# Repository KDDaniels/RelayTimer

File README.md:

# Relay Timer

Simple timer with a two button interface and LCD screen to show the time remaining. Intended to control a relay but could be used for anything else really.

# Dependencies

I couldn't find it on the PlatformIO library explorer, but this project requires the **[LiquidCrystal_attiny](https://github.com/platisd/ATtiny85-LCD-library/tree/master)** library.

## Features:
- Adjustable time, goes up to 9:59:59 max by default but can be adjusted
- Timer is pausable whenever needed
- Can easily reset the timer while paused or before starting

## Wiring

Intended for an **ATtiny85**, this could definitely be ported to other microcontrollers if needed. Will need slight adjustment due to the direct port register manipulation though.

- NC = No connection
- FB = Function button
- TB = Toggle button
- SCL goes to SCL
- SDA goes to SDA
- Relay goes to a transistor (or straight to a relay if you're feeling bold (don't do that))

```
             ATtiny85
             __   __
 NC <- PB5 =|1 *-* 8|= VCC <- +5v
 FB <- PB3 =|2     7|= PB2 -> SCL
 TB <- PB4 =|3     6|= PB1 -> Relay
GND <- GND =|4_____5|= PB0 -> SDA

```

# Hardware
- ATtiny85 or another microcontroller (will require modification)
- LCD with I<sup>2</sup>C support (I'm using a 1602 screen with a PCF8574 board)
- A relay module
- Two buttons
- A single NPN transistor (I'm using a 2N2222)
- A few resistors (2 4.7kOhm and 5 1kOhm)

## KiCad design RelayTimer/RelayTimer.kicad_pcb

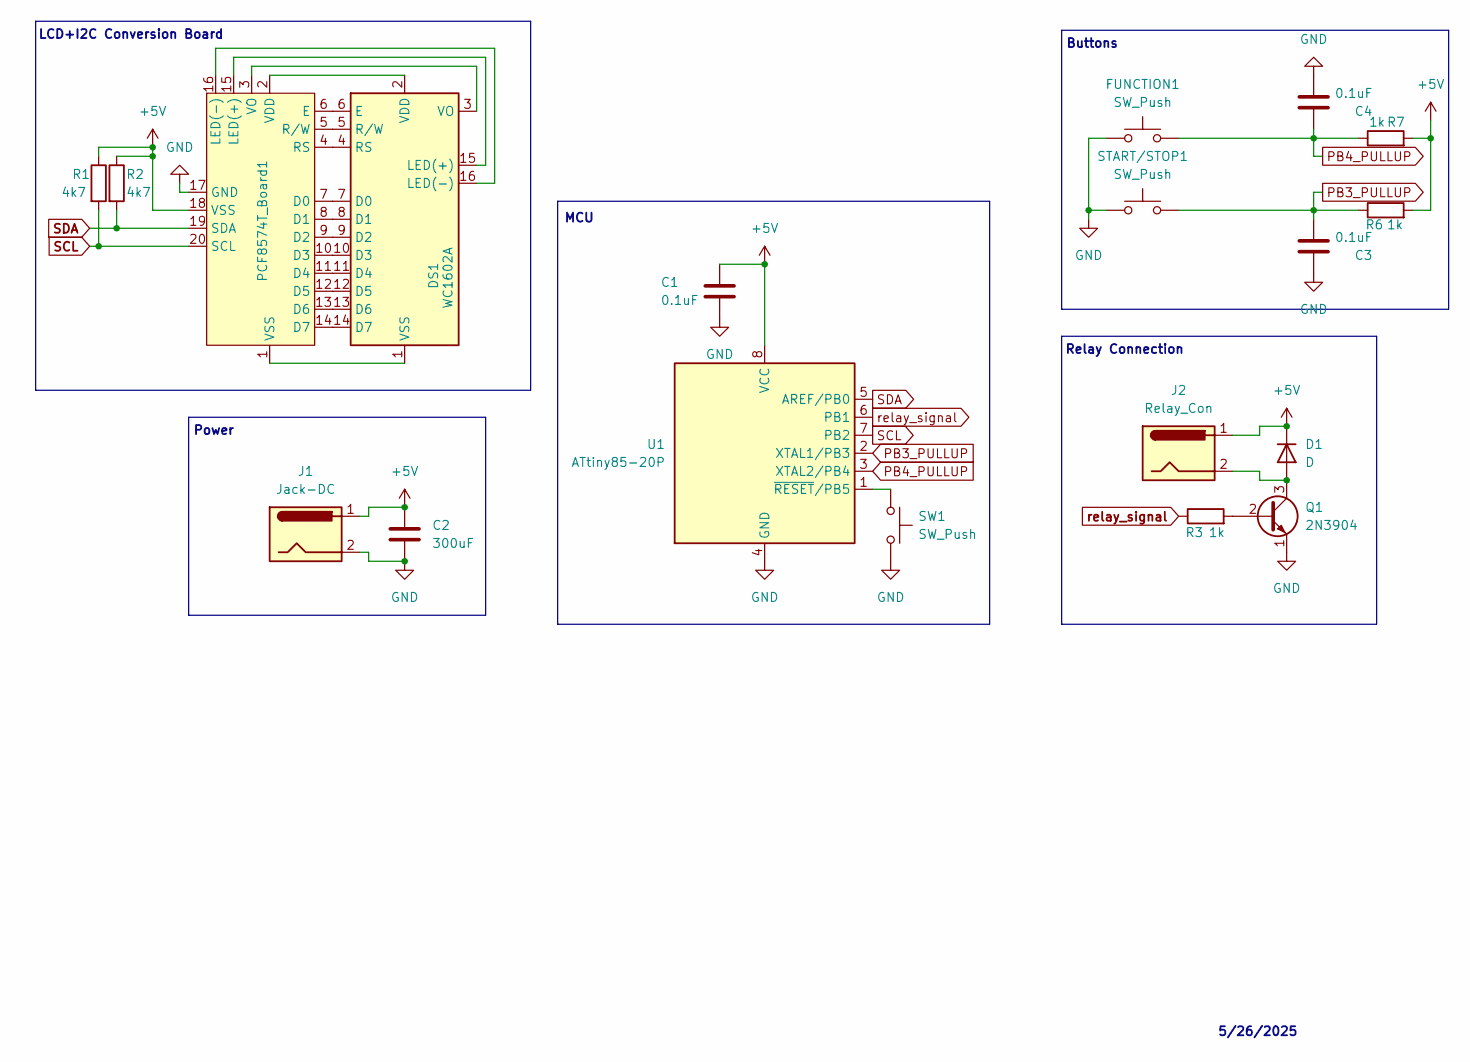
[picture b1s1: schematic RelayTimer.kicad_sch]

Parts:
C1, C3, C4: 0.1uF; C_Disc_D3.0mm_W1.6mm_P2.50mm
C2: 300uF; C_Radial_D10.0mm_H12.5mm_P5.00mm
D1: D; D_DO-41_SOD81_P2.54mm_Vertical_KathodeUp
DS1: WC1602A
FUNCTION1: SW_Push; SW_PUSH-12mm
J1: Jack-DC; BarrelJack_GCT_DCJ200-10-A_Horizontal
J2: Relay_Con; BarrelJack_GCT_DCJ200-10-A_Horizontal
PCF8574T_Board1: PCF8574T
Q1: 2N3904; TO-92
R1, R2: 4k7; R_Axial_DIN0204_L3.6mm_D1.6mm_P2.54mm_Vertical
R3: 1k; R_Axial_DIN0204_L3.6mm_D1.6mm_P2.54mm_Vertical
R6, R7: 1k; R_Axial_DIN0204_L3.6mm_D1.6mm_P7.62mm_Horizontal
START/STOP1: SW_Push; SW_PUSH-12mm
SW1: SW_Push; SW_PUSH_6mm
U1: ATtiny85-20P; DIP-8_W7.62mm

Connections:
+5V: C1.2, C2.1, D1.1 (K), J1.1, J2.1, PCF8574T_Board1.18 (VSS), R1.1, R2.1, R6.2, R7.2, U1.8 (VCC)
GND: C1.1, C2.2, C3.2, C4.1, FUNCTION1.1, J1.2, PCF8574T_Board1.17 (GND), Q1.1 (E), START/STOP1.1, SW1.2, U1.4 (GND)
unnamed: D1.2 (A), J2.2, Q1.3 (C)
unnamed: DS1.7 (D0), PCF8574T_Board1.7 (D0)
unnamed: DS1.8 (D1), PCF8574T_Board1.8 (D1)
unnamed: DS1.9 (D2), PCF8574T_Board1.9 (D2)
unnamed: DS1.10 (D3), PCF8574T_Board1.10 (D3)
unnamed: DS1.11 (D4), PCF8574T_Board1.11 (D4)
unnamed: DS1.12 (D5), PCF8574T_Board1.12 (D5)
unnamed: DS1.13 (D6), PCF8574T_Board1.13 (D6)
unnamed: DS1.14 (D7), PCF8574T_Board1.14 (D7)
unnamed: DS1.6 (E), PCF8574T_Board1.6 (E)
unnamed: DS1.15 (LED(+)), PCF8574T_Board1.15 (LED(+))
unnamed: DS1.16 (LED(-)), PCF8574T_Board1.16 (LED(-))
unnamed: DS1.4 (RS), PCF8574T_Board1.4 (RS)
unnamed: DS1.5 (R/W), PCF8574T_Board1.5 (R/W)
unnamed: DS1.2 (VDD), PCF8574T_Board1.2 (VDD)
unnamed: DS1.3 (VO), PCF8574T_Board1.3 (VO)
unnamed: DS1.1 (VSS), PCF8574T_Board1.1 (VSS)
unnamed: Q1.2 (B), R3.2
unnamed: SW1.1, U1.1 (~RESET/PB5)
PB3_PULLUP: C3.1, R6.1, START/STOP1.2, U1.2 (XTAL1/PB3)
PB4_PULLUP: C4.2, FUNCTION1.2, R7.1, U1.3 (XTAL2/PB4)
SCL: PCF8574T_Board1.20 (SCL), R1.2, U1.7 (PB2)
SDA: PCF8574T_Board1.19 (SDA), R2.2, U1.5 (AREF/PB0)
relay_signal: R3.1, U1.6 (PB1)

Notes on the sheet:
Relay Connection
Power
5/26/2025
Buttons
MCU
LCD+I2C Conversion Board

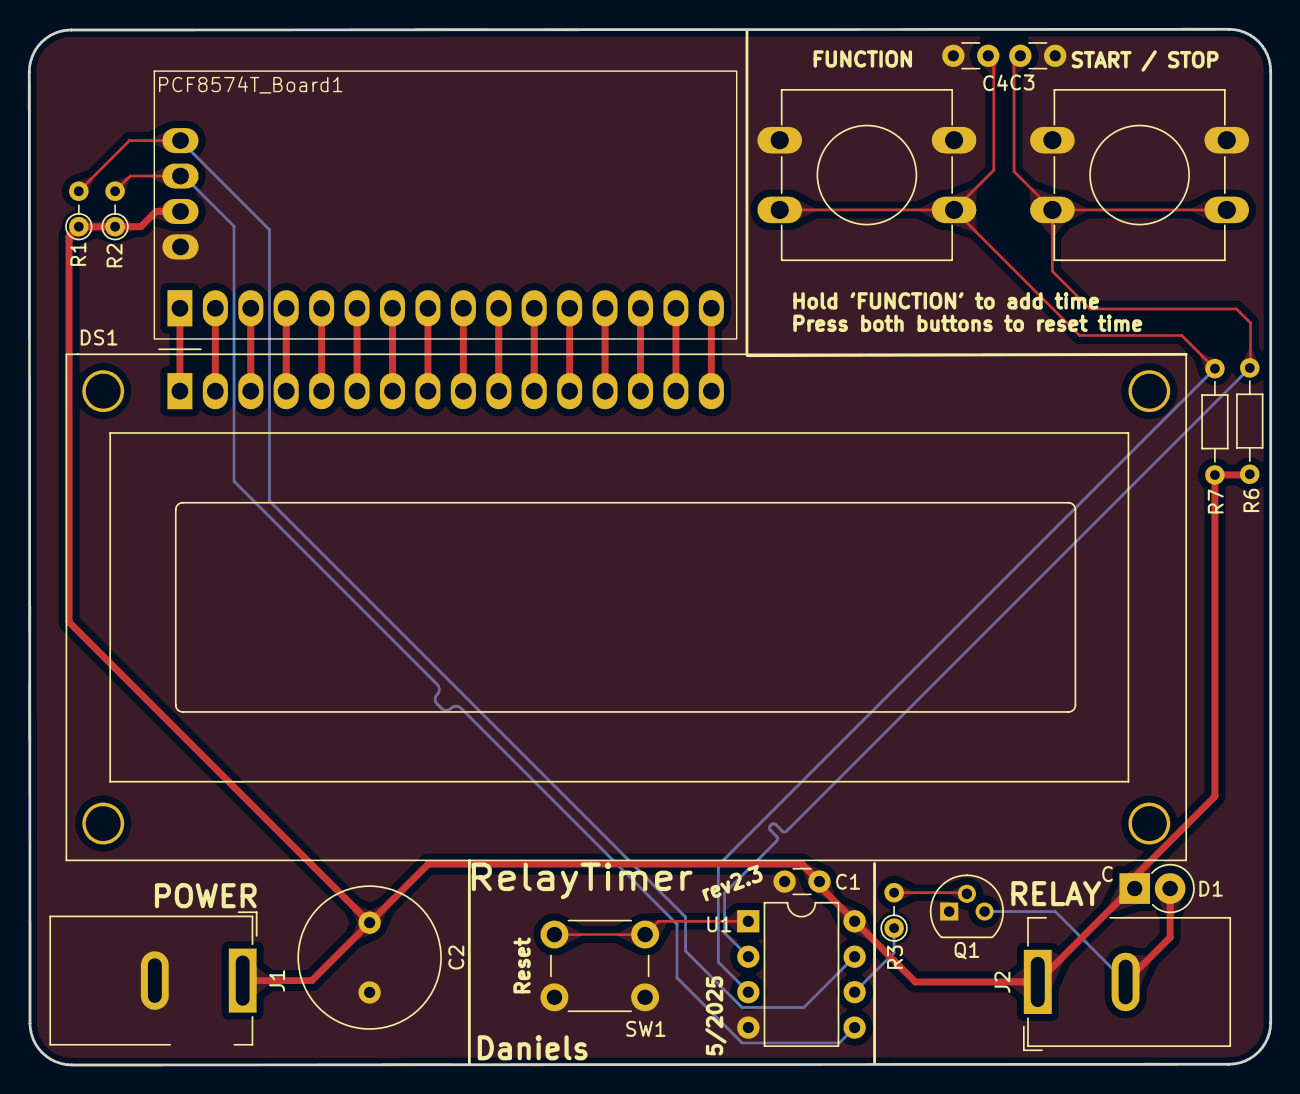
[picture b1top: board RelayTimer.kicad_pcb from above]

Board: 2 copper layers, 89.0 x 74.3 mm, 19 parts (0 on the bottom side), 26 nets.

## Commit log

2025-05-28 created PlatformIO defaults
2025-05-28 switched to uploading using Arduino as ISP
2025-05-28 split functions into separate files and namespaces
2025-05-28 basic display functions implemented
2025-05-28 slight change in arg types
2025-05-28 changed it back because I'm a goober
2025-05-28 basic relay functions implemented
2025-05-28 basic testing functionality implemented
2025-05-28 minor update
2025-05-28 added PCB project files
2025-05-28 added a couple combo functions
2025-05-29 added some stuff to timer
2025-05-29 updated main a bit
2025-05-29 added enable/disable functions to relay
2025-05-29 updated folder name
2025-05-29 cleaned up file structure a bit
2025-05-29 simplified timer functionality
2025-05-29 updated button functionality
2025-05-29 updated relay to use basic port manipulation
2025-05-29 updated buttons to use basic port manipulation
2025-05-29 small update to relay
2025-05-29 added license
2025-05-29 removed unnecessary dependencies
2025-05-29 added a few button functions
2025-05-29 fixed elusive issue with pausing
2025-05-29 program functional (without bugs hopefully)
2025-05-29 fixed formatting
2025-05-29 removed unneeded file
2025-05-30 added rollover protection
2025-05-30 added rollover protection that actually works
2025-05-30 minor update to KiCad project
2025-05-30 minor update to gitignore
2025-05-30 added small reset button to schematic
2025-05-30 forgot to update the revision number
2025-06-02 fixed typo
2025-06-13 fixed small issue and updated board
2025-06-13 removed a tiny hidden trace
2025-06-13 added support structure STL
